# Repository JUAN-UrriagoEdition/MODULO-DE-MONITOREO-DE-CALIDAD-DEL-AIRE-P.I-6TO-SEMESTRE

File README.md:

# 🌬️ Estación Modular de Calidad del Aire (AQ)
### Módulo de Gases Electroquímicos — Ingeniería Electrónica, UCEVA 2026

<div align="center">

</div>

---

## 📋 Descripción General

Este repositorio documenta el **Módulo de Gases Electroquímicos** de la Estación Modular de Calidad del Aire (AQ), desarrollado como proyecto integrador de 6to semestre en la **Facultad de Ingeniería Electrónica de la Unidad Central del Valle del Cauca (UCEVA)**.

El módulo mide en tiempo real las concentraciones de **monóxido de carbono (CO)**, **dióxido de nitrógeno (NO₂)**, **CO₂ equivalente** y **compuestos orgánicos volátiles (COV)** tanto en entornos interiores como exteriores, publicando los datos a un dashboard web mediante WiFi.

> 📄 **[Descargar Informe Técnico Completo (WORD)](./ESTACION_AQ_ACTUALIZADO.docx)**
> 📄 **[Descargar Repositorio (.bat)](./Descargar_Repo_Monitor_de_Gases.bat)**

---

## 🎯 Motivación

La contaminación del aire representa uno de los mayores problemas de salud pública a nivel mundial. En el municipio de **Tuluá y el Valle del Cauca**, la ausencia de redes densas de monitoreo continuo limita la detección oportuna de episodios críticos de contaminación, especialmente en corredores viales de alto tráfico y en espacios interiores de instituciones educativas.

Los sistemas convencionales de monitoreo tienen costos de entre **USD 50.000 y 200.000** por estación. Este módulo propone una alternativa de **bajo costo** basada en sensores MEMS, con criterios rigurosos de instrumentación, calibración y validación.

---

## ⚙️ Arquitectura del Sistema

La cadena de instrumentación sigue el flujo completo:

```
Sensor MEMS → Filtro RC (fc ≈ 10.6 Hz) → Buffer LMV321 → ADC 12-bit ESP32-S3 → Procesamiento → WiFi → Hub → Dashboard
```

El sensor digital **CCS811** se conecta directamente por bus **I²C**, sin requerir acondicionamiento analógico externo.

---

## 🔬 Sensores y Componentes Principales

| Componente | Función | Interfaz |
|---|---|---|
| **SEN0564** (DFRobot) | CO — 5 a 5000 ppm | Analógica (0.4–2.0 V) |
| **SEN0574** (DFRobot) | NO₂ — 0.1 a 10 ppm | Analógica |
| **CCS811** (ScioSense) | CO₂eq + TVOC | Digital I²C |
| **ESP32-S3-WROOM-1U** | MCU, ADC 12-bit, WiFi | — |
| **LMV321** | Buffer seguidor de voltaje | — |
| **REF2033A** | Referencia de voltaje dual 3.3/1.65 V | — |
| **LP38692MP-3.3** | Regulador LDO 3.3 V | — |
| **LED RGB** | Indicación visual de calidad del aire | PWM |

---

## 📐 Diseño de Acondicionamiento Analógico

- **Filtro RC pasabajas** de primer orden: `R = 10 kΩ`, `C = 1.5 µF` → `fc ≈ 10.6 Hz`
- **Buffer LMV321** en configuración seguidor unitario (ganancia 1) para desacoplar la impedancia del ADC
- **Referencia REF2033A** con baja deriva térmica para estabilidad en la conversión ADC
- **ADC SAR de 12 bits** del ESP32-S3: resolución teórica de `≈ 0.806 mV/bit`
- **Sobremuestreo y promediado** (N = 32–64 muestras) para mejorar la resolución efectiva (ENOB ≥ 11 bits)

---

## 💡 Indicación Visual

El LED RGB indica el nivel de calidad del aire mediante colores controlados por PWM (5 kHz, 8 bits):

| Color | Estado | Umbral |
|---|---|---|
| 🟢 Verde | Limpio | < 40% de escala |
| 🟡 Ámbar | Advertencia | 40–70% de escala |
| 🔴 Rojo | Crítico | > 70% de escala |

---

## 📡 Formato de Mensajes JSON (Contrato de Datos)

El módulo publica al hub central mensajes con la siguiente estructura mínima:

```json
{
  "module": "gas_module_01",
  "environment": "indoor",
  "location": "UCEVA - Aula 201",
  "ts": 1745000000,
  "metrics": {
    "co_ppm": 1.2,
    "no2_ppm": 0.05,
    "eco2_ppm": 520,
    "tvoc_ppb": 35,
    "quality": "ok",
    "temp_comp": 24.5,
    "rh_comp": 58.0
  }
}
```

---

## 🔄 Estados del Firmware

| Estado | Descripción |
|---|---|
| `warmup` | Calentamiento inicial del sensor (< 2 min) |
| `ok` | Operación normal |
| `fault` | Sensor desconectado o señal fuera de rango |
| `saturation` | Señal en los extremos del rango ADC |
| `suspect` | Alta variabilidad o lecturas inconsistentes |

---

## 📦 Lista de Materiales (BOM)

Los componentes fueron adquiridos mediante el pedido **Mouser N.° 279751168** (enviado el 21 de abril de 2026). El costo total del pedido fue de aproximadamente **USD 48** más aranceles de importación colombianos.

Los sensores SEN0564, SEN0574 y el LED RGB se adquirieron de forma local/separada.

---

## 🧪 Pruebas y Criterios de Aceptación

| ID | Prueba | Criterio |
|---|---|---|
| CP01 | Rango analógico SEN0564 (CO) | V_out varía de forma monotónica en 0.4–2.0 V |
| CP04 | Respuesta del filtro RC | Atenuación a fc = −3 dB ± 1 dB; a 10·fc ≥ −20 dB |
| CP06 | Publicación de mensajes JSON | ≥ 5 mensajes válidos en 5 minutos |
| CP07 | Estado warmup al encender | `quality = warmup` durante ≥ 60 s |
| CP08 | Estado fault ante desconexión | `quality = fault` en ≤ 3 ciclos de publicación |

---

## 👥 Equipo

| Nombre | Código |
|---|---|
| David Ortega Ruiz | 240232001 |
| Juan Fernando Urriago Hernández | 240232002 |
| Sergio Peñaranda Agudelo | 240232004 |
| Miguel Ángel Parra Gutiérrez | 240232013 |

**Asignatura integradora:** Instrumentación I  
**Docente:** Álvaro Hernando Salazar Victoria  
**Facultad de Ingeniería Electrónica — UCEVA, 2026**

---

## 📚 Referencias Clave

- Mead et al. (2013) — *Atmospheric Environment* — Redes urbanas con sensores electroquímicos
- Kumar et al. (2015) — *Environment International* — Sensores de bajo costo para calidad del aire
- Spinelle et al. (2015) — *Sensors and Actuators B* — Calibración en campo con MLR
- Zimmerman et al. (2018) — *Atmospheric Measurement Techniques* — Calibración con Random Forest

---

> 📄 **[Descargar Informe Técnico Completo (PDF)](./ESTACIÓN_MODULAR_DE_CALIDAD_DEL_AIRE.pdf)**

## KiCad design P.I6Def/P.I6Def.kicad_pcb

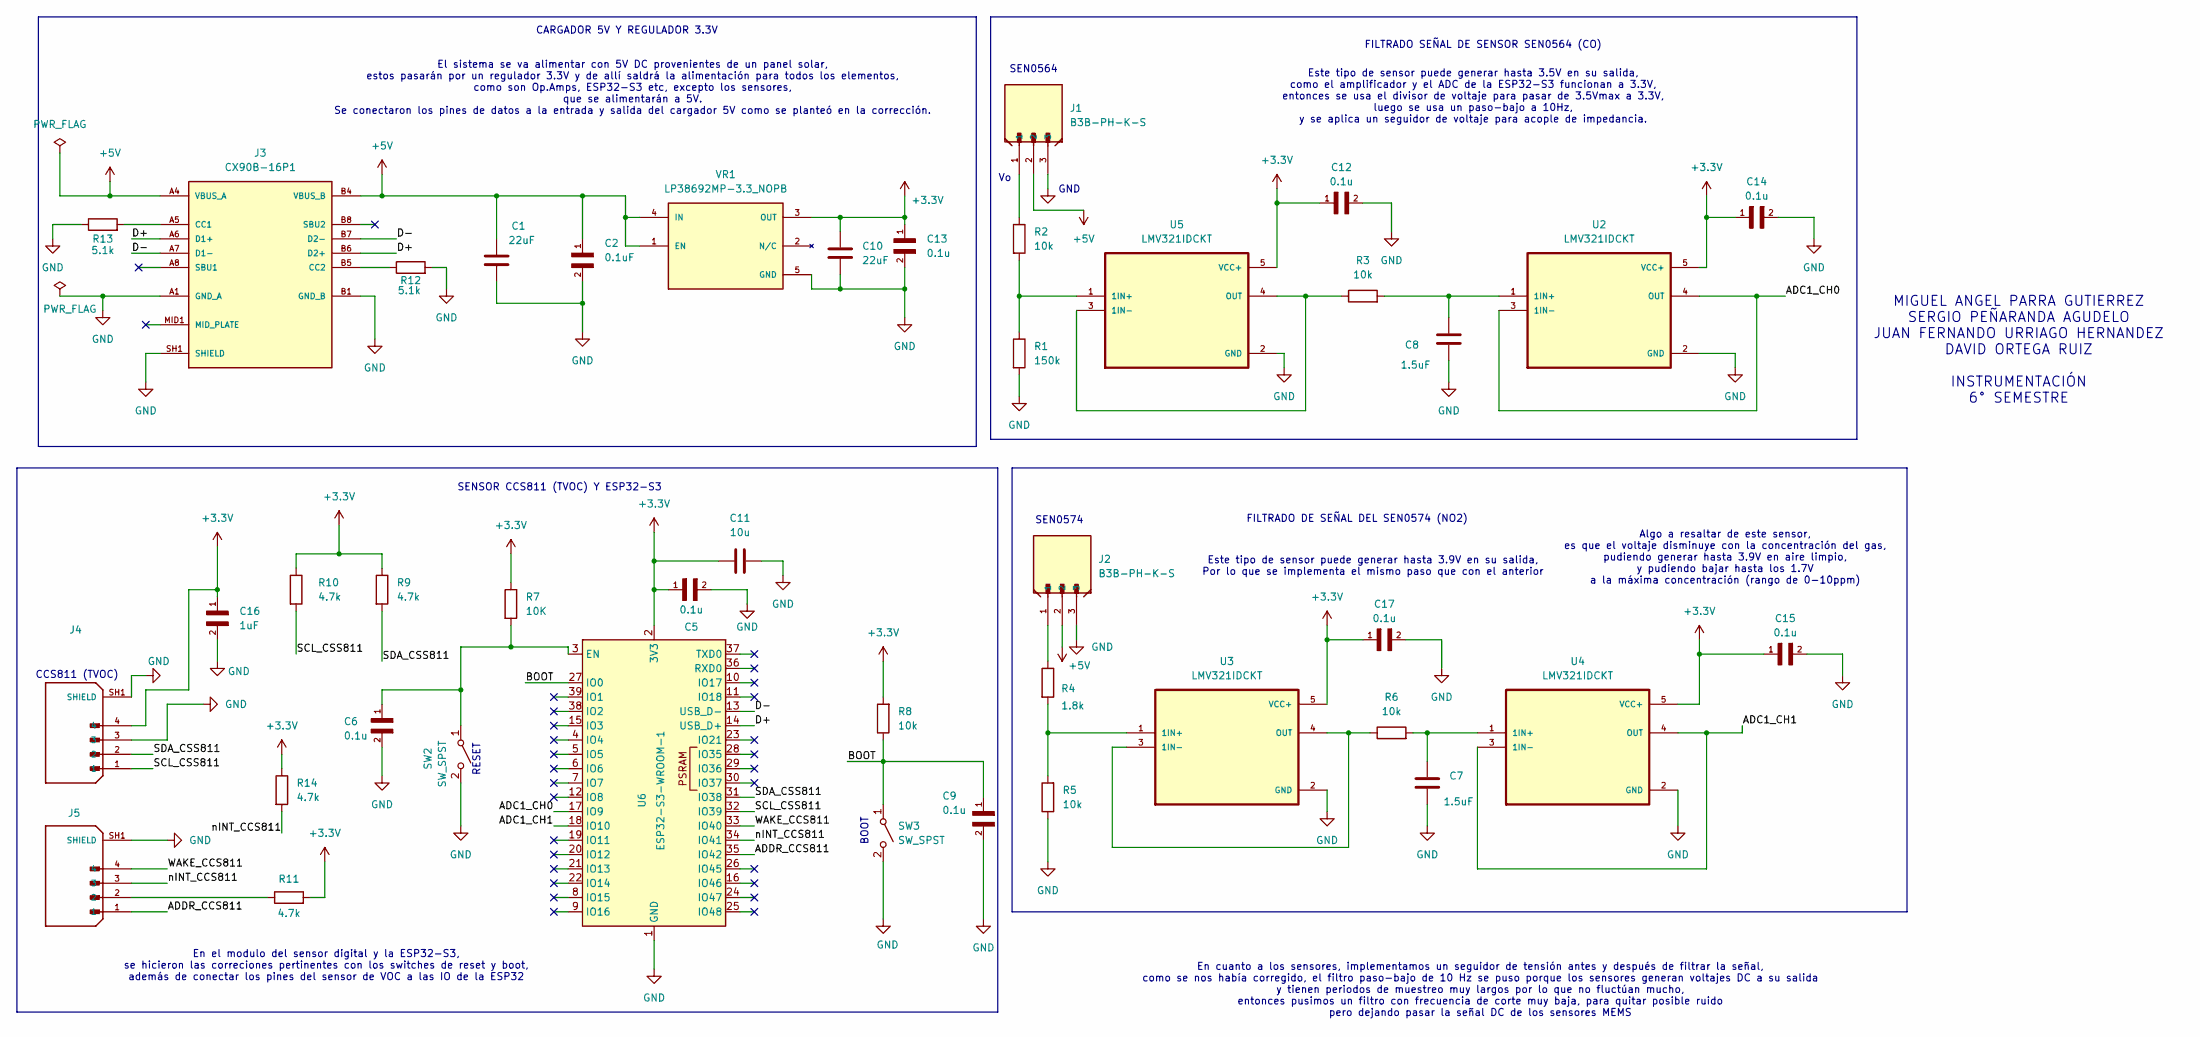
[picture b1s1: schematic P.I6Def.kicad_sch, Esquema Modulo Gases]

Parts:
C1, C10: 22uF; CAPC2012X140N
C2: 0.1uF; CAPC2012X88N
C5, C6, C9, C12, C13, C14, C15, C17: 0.1u; CAPC2012X88N
C7, C8: 1.5uF; CAPC2012X145N
C11: 10u; CAPC2012X145N
C16: 1uF; CAPC2012X100N
J1, J2: B3B-PH-K-S; JST_B3B-PH-K-S
J3: CX90B-16P1; HIROSE_CX90B-16P1; PARTREV 23.04.05
J4, J5: B4B-PH-SM4-TB_LF__SN__P_; JST_B4B-PH-SM4-TB_LF__SN__P_; PARTREV N/A
R1: 150k; RES_ERA6AEB154V
R2, R3, R5, R6, R8: 10k; RESC2012X55N
R4: 1.8k; RES_ERA6AEB182V
R7: 10K; RESC2012X55N
R9, R10, R11, R14: 4.7k; RES_ERA6AEB472V
R12, R13: 5.1k; RESC2012X55N
SW2, SW3: SW_SPST; SW_TS04-66-85-BK-160-SMT-TR
U2, U3, U4, U5: LMV321IDCKT; SOT65P210X110-5N
U6: ESP32-S3-WROOM-1; ESP32-S3-WROOM-1U
VR1: LP38692MP-3.3_NOPB; SOT150P700X180-5N; PARTREV M

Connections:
+3.3V: C5.1, C10.1, C11.1, C12.1, C13.1, C14.1, C15.1, C16.1, C17.1, J4.4, R7.1, R8.2, R9.1, R10.1, R11.2, R14.1, U2.5 (VCC+), U3.5 (VCC+), U4.5 (VCC+), U5.5 (VCC+), U6.2 (3V3), VR1.3 (OUT)
+5V: C1.1, C2.1, J1.2, J2.2, J3.A4 (VBUS_A), J3.A9 (VBUS_A), J3.B4 (VBUS_B), J3.B9 (VBUS_B), VR1.1 (EN), VR1.4 (IN)
/ADC1_CH0: U2.3 (1IN-), U2.4 (OUT), U6.17 (IO9)
/ADC1_CH1: U4.3 (1IN-), U4.4 (OUT), U6.18 (IO10)
/ADDR_CCS811: J5.1, U6.35 (IO42)
/BOOT: C9.1, R8.1, SW3.1 (A), U6.27 (IO0)
/D+: J3.A6 (D1+), J3.B6 (D2+), U6.14 (USB_D+)
/D-: J3.A7 (D1-), J3.B7 (D2-), U6.13 (USB_D-)
/SCL_CSS811: J4.1, R10.2, U6.32 (IO39)
/SDA_CSS811: J4.2, R9.2, U6.31 (IO38)
/WAKE_CCS811: J5.4, U6.33 (IO40)
/nINT_CCS811: J5.3, R14.2, U6.34 (IO41)
GND: C1.2, C2.2, C5.2, C6.2, C7.2, C8.2, C9.2, C10.2, C11.2, C12.2, C13.2, C14.2, C15.2, C16.2, C17.2, J1.3, J2.3, J3.A1 (GND_A), J3.A12 (GND_A), J3.B1 (GND_B), J3.B12 (GND_B), J3.SH1 (SHIELD), J3.SH2 (SHIELD), J3.SH3 (SHIELD), J3.SH4 (SHIELD), J3.SH5 (SHIELD), J3.SH6 (SHIELD), J4.3, J4.SH1 (SHIELD), J4.SH2 (SHIELD), J5.SH1 (SHIELD), J5.SH2 (SHIELD), R1.2, R5.1, R12.2, R13.1, SW2.2 (B), SW3.2 (B), U2.2 (GND), U3.2 (GND), U4.2 (GND), U5.2 (GND), U6.1 (GND), U6.40 (GND), U6.41 (GND), VR1.5 (GND)
unnamed: J1.1, R2.1
unnamed: J2.1, R4.1
unnamed: J3.A5 (CC1), R13.2
unnamed: J3.B5 (CC2), R12.1
unnamed: J5.2, R11.1
unnamed: C6.1, R7.2, SW2.1 (A), U6.3 (EN)
unnamed: C8.1, R3.2, U2.1 (1IN+)
unnamed: R4.2, R5.2, U3.1 (1IN+)
unnamed: R6.1, U3.3 (1IN-), U3.4 (OUT)
unnamed: C7.1, R6.2, U4.1 (1IN+)
unnamed: R1.1, R2.2, U5.1 (1IN+)
unnamed: R3.1, U5.3 (1IN-), U5.4 (OUT)

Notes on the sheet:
Algo a resaltar de este sensor, es que el voltaje disminuye con la concentración del gas, pudiendo generar hasta 3.9V en aire limpio, y pudiendo bajar hasta los 1.7V a la máxima concentración (rango de 0-10ppm)
SEN0574
MIGUEL ANGEL PARRA GUTIERREZ SERGIO PEÑARANDA AGUDELO JUAN FERNANDO URRIAGO HERNANDEZ DAVID ORTEGA RUIZ INSTRUMENTACIÓN 6° SEMESTRE
RESET
Este tipo de sensor puede generar hasta 3.9V en su salida, Por lo que se implementa el mismo paso que con el anterior
En cuanto a los sensores, implementamos un seguidor de tensión antes y después de filtrar la señal, como se nos había corregido, el filtro paso-bajo de 10 Hz se puso porque los sensores generan voltajes DC a su salida y tienen periodos de muestreo muy largos por lo que no fluctúan mucho, entonces p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
El sistema se va alimentar con 5V DC provenientes de un panel solar, estos pasarán por un regulador 3.3V y de allí saldrá la alimentación para todos los elementos, como son Op.Amps, ESP32-S3 etc, excepto los sensores, que se alimentarán a 5V. Se conectaron los pines de datos a la entrada y salida d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
CARGADOR 5V Y REGULADOR 3.3V
SENSOR CCS811 (TVOC) Y ESP32-S3
FILTRADO SEÑAL DE SENSOR SEN0564 (CO)
SEN0564
Este tipo de sensor puede generar hasta 3.5V en su salida, como el amplificador y el ADC de la ESP32-S3 funcionan a 3.3V, entonces se usa el divisor de voltaje para pasar de 3.5Vmax a 3.3V, luego se usa un paso-bajo a 10Hz, y se aplica un seguidor de voltaje para acople de impedancia.
En el modulo del sensor digital y la ESP32-S3, se hicieron las correciones pertinentes con los switches de reset y boot, además de conectar los pines del sensor de VOC a las IO de la ESP32
GND
CCS811 (TVOC)
FILTRADO DE SEÑAL DEL SEN0574 (NO2)
BOOT

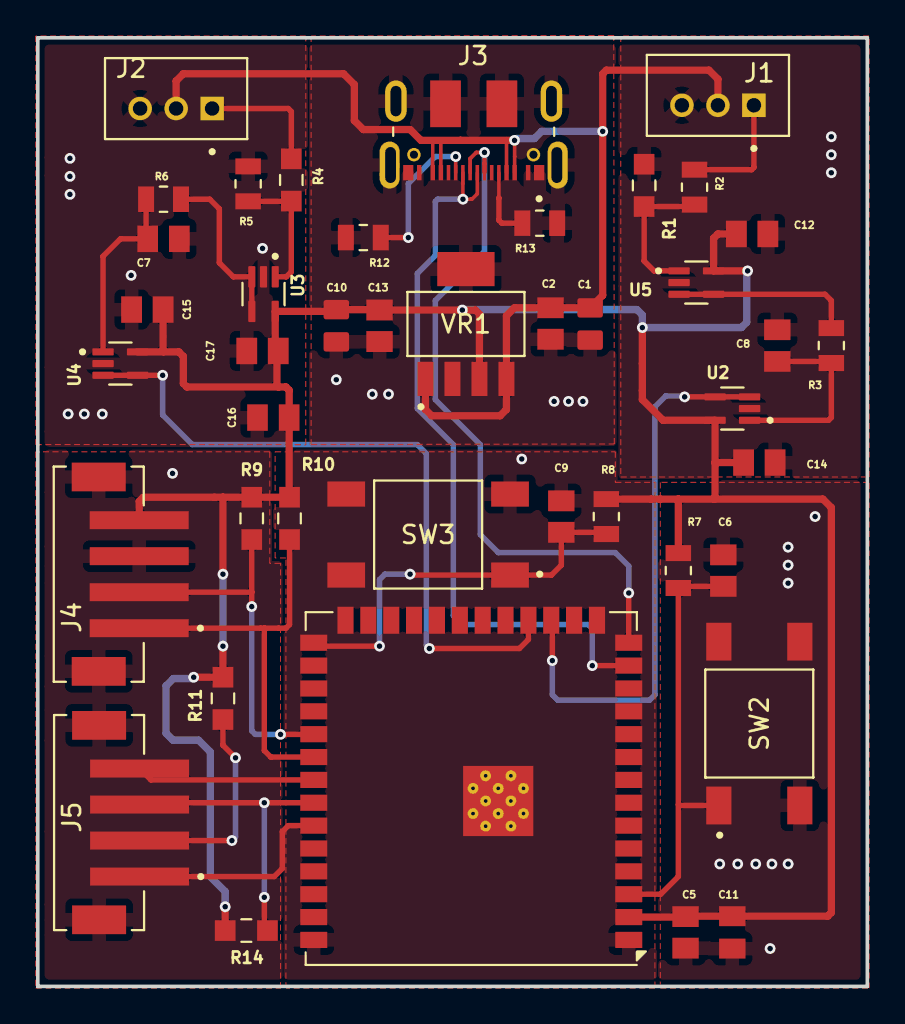
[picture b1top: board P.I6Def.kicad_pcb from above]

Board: 2 copper layers, 46.1 x 52.7 mm, 42 parts (0 on the bottom side), 25 nets.

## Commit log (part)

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2026-04-18 avance footprints
2026-04-25 Primer avance interfaz grafica
2026-04-25 Adjunto la cotización en Mouser
2026-04-25 Ayuda para subir automaticamente el repositorio
2026-04-25 Descarga Automatica del repositorio para colaboradores
2026-04-25 Demo .bat
2026-04-25 Demo
2026-04-25 Actualizacion
2026-04-25 Actualizacion estetica
2026-05-08 Se implementaron las correcciones planteadas
2026-05-08 .bat para descargar repo
2026-05-08 Añado .bat para actualizar Repositorio
2026-05-08 esto es una prueba
2026-05-08 Prueba
2026-05-08 agregue los componentes al pcb
2026-05-08 Interfaz grafica descomprimida
2026-05-08 README Actualizado
2026-05-08 Adjunto Informe
2026-05-08 Adjunto Word Del informe
2026-05-08 Archivo Word del Informe
2026-05-08 Archivo descarga repo
2026-05-12 ACTUALIZACION DE TAMAÑO PCB
2026-05-14 MEJORA DE LA PCB
2026-05-15 Actualizacion PCB
2026-05-18 ACTUALIZACION DE LAS PISTAS DE LA PCB
2026-05-20 terminar conecciones y reorganizar los componentes
2026-05-20 Relleno de Cobre
2026-05-21 Solucion de errores y advertencias de DRC
2026-05-22 fix: correcciones de DRC - falta corregir alivios term y 45grad
2026-05-22 Correcciones planos de tierra
2026-05-23 Creacion de archivos gerber
2026-05-26 Programacion IDE ESP32-S3 (Primer Versón)
2026-05-29 Imagen del primer prototipo (Alpha)
2026-05-29 Subo imagen del primer prototipo (Conceptualizacion)
2026-05-29 MODIFICACION AL INFORME
2026-05-29 Adjunto la programacion de la interfaz y ESP32 del ultimo prototipo
2026-06-02 Correccion de cagada de miguel
2026-06-04 Creacion de app
2026-06-04 Adjunto la ultima version del PI
2026-06-04 ACTUALIZACION INFORME
2026-06-04 Actualizacion de documento
2026-06-04 act informe
2026-06-04 Mejora de la programacion de la ESP32S3
2026-06-04 Act Word
2026-06-04 Archivo de la informacion de la Dashboard
2026-06-04 Aporte Documento Final
2026-06-05 Informe del Proyecto en formato pdf
